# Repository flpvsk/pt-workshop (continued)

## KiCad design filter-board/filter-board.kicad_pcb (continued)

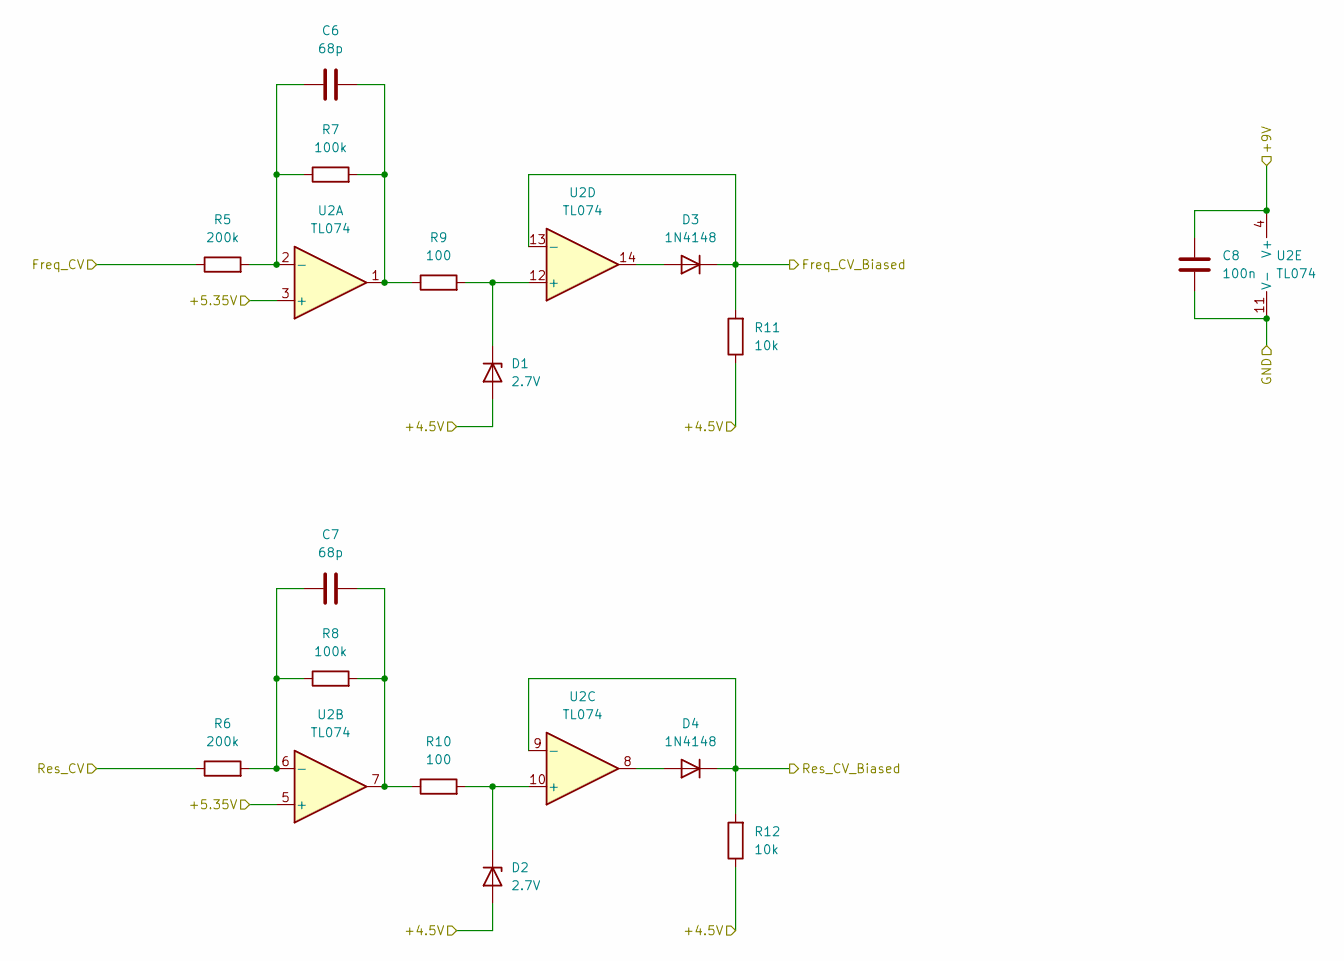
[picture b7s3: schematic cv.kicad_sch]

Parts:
C6, C7: 68p; C_0603_1608Metric_Pad1.08x0.95mm_HandSolder; LCSC C1680
C8: 100n; C_0603_1608Metric_Pad1.08x0.95mm_HandSolder; LCSC C76711
D1, D2: 2.7V; D_SOD-123; LCSC C406712
D3, D4: 1N4148; D_SOD-123; LCSC C81598
R5, R6: 200k; R_0603_1608Metric_Pad0.98x0.95mm_HandSolder; LCSC C25811
R7, R8: 100k; R_0603_1608Metric_Pad0.98x0.95mm_HandSolder; LCSC C25803
R9, R10: 100; R_0603_1608Metric_Pad0.98x0.95mm_HandSolder; LCSC C22775
R11, R12: 10k; R_0603_1608Metric_Pad0.98x0.95mm_HandSolder; LCSC C25804
U2: TL074; SOIC-14_3.9x8.7mm_P1.27mm; LCSC C6963

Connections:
/+4.5V_Buf: D1.2 (A), D2.2 (A), R11.1, R12.1; also elsewhere on the board
/+5.35V_Buf: U2.3 (+), U2.5 (+); also elsewhere on the board
/+9V: C8.2, U2.4 (V+); also elsewhere on the board
/CV Processing/Freq_CV_Biased: D3.1 (K), R11.2, U2.13 (-); also elsewhere on the board
/CV Processing/Res_CV_Biased: D4.1 (K), R12.2, U2.9 (-); also elsewhere on the board
/Freq_CV: R5.1; also elsewhere on the board
/GND: C8.1, U2.11 (V-); also elsewhere on the board
/Res_CV: R6.1; also elsewhere on the board
unnamed: C6.1, R5.2, R7.1, U2.2 (-)
unnamed: C6.2, R7.2, R9.1, U2.1
unnamed: C7.1, R6.2, R8.1, U2.6 (-)
unnamed: C7.2, R8.2, R10.1, U2.7
unnamed: D1.1 (K), R9.2, U2.12 (+)
unnamed: D2.1 (K), R10.2, U2.10 (+)
unnamed: D3.2 (A), U2.14
unnamed: D4.2 (A), U2.8

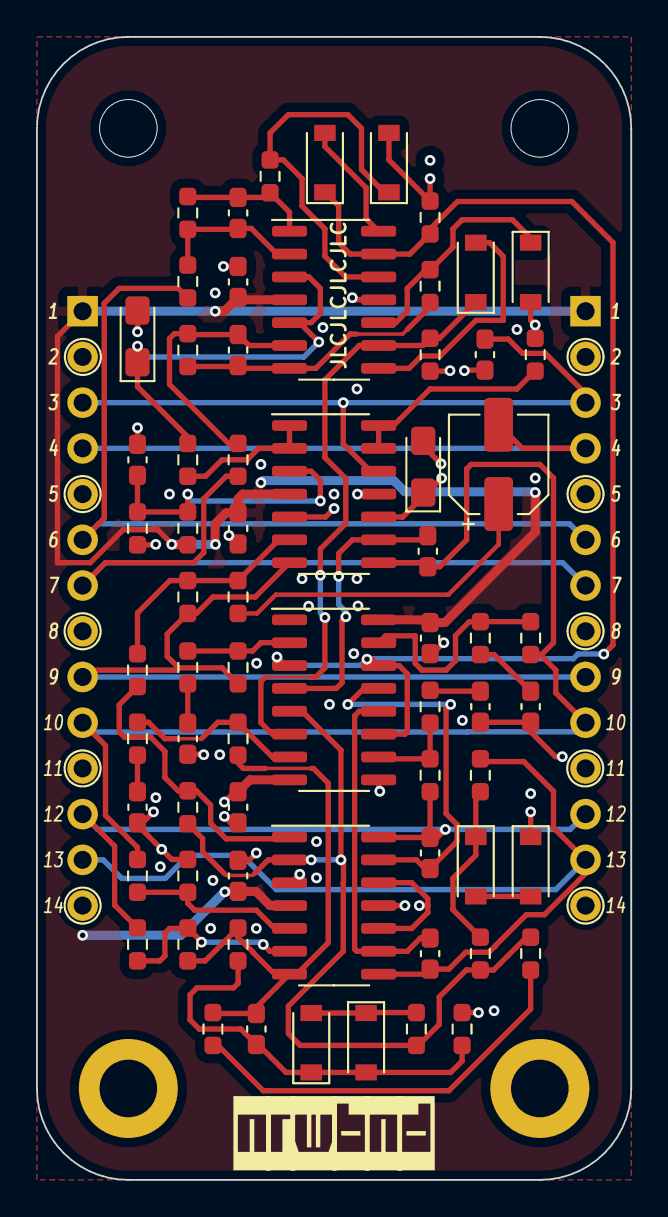
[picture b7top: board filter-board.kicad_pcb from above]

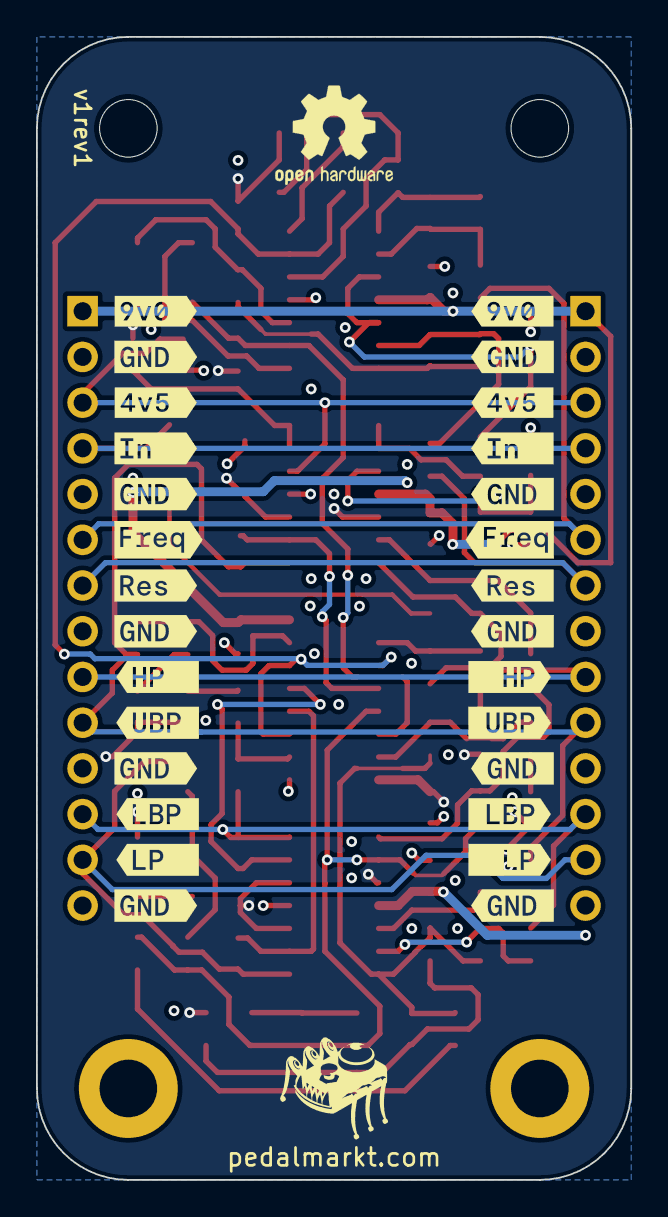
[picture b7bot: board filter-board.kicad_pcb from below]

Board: 4 copper layers, 33.0 x 63.5 mm, 102 parts (30 on the bottom side), 48 nets.

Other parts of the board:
kibuzzard-666B0D3F: G***; kibuzzard-666B0D3F
kibuzzard-666B0D4B, kibuzzard-666B0D4B#2, kibuzzard-666B0D4B#3, kibuzzard-666B0D4B#4, kibuzzard-666B0D4B#5: G***; kibuzzard-666B0D4B
kibuzzard-666B0D6E: G***; kibuzzard-666B0D6E
kibuzzard-666B0D54: G***; kibuzzard-666B0D54
kibuzzard-666B0D65: G***; kibuzzard-666B0D65
kibuzzard-666B0D69, kibuzzard-666B0D69#2, kibuzzard-666B0D69#3, kibuzzard-666B0D69#4, kibuzzard-666B0D69#5: G***; kibuzzard-666B0D69
kibuzzard-666D7707: G***; kibuzzard-666D7707
kibuzzard-6673DFE6: G***; kibuzzard-6673DFE6
kibuzzard-6673E32C: G***; kibuzzard-6673E32C
kibuzzard-6673E33D: G***; kibuzzard-6673E33D
kibuzzard-6673E38A: G***; kibuzzard-6673E38A
kibuzzard-6673E097: G***; kibuzzard-6673E097
kibuzzard-6673E301: G***; kibuzzard-6673E301
kibuzzard-6673E306: G***; kibuzzard-6673E306
kibuzzard-6673E326: G***; kibuzzard-6673E326
kibuzzard-6673E332: G***; kibuzzard-6673E332
kibuzzard-6673E338: G***; kibuzzard-6673E338
kibuzzard-6673E342: G***; kibuzzard-6673E342
kibuzzard-6673E377: G***; kibuzzard-6673E377
kibuzzard-6673E380: G***; kibuzzard-6673E380
kibuzzard-6673E386: G***; kibuzzard-6673E386

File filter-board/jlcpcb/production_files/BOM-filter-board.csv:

Comment,Designator,Footprint,LCSC
220p,"C10,C13,C15,C18",C_0603_1608Metric_Pad1.08x0.95mm_HandSolder,C106210
22u,"C3,C4",CP_EIA-3216-18_Kemet-A_Pad1.58x1.35mm_HandSolder,C129272
68p,"C6,C7",C_0603_1608Metric_Pad1.08x0.95mm_HandSolder,C1680
100,"R10,R9",R_0603_1608Metric_Pad0.98x0.95mm_HandSolder,C22775
10,"R3,R4",R_0603_1608Metric_Pad0.98x0.95mm_HandSolder,C22859
220,"R24,R25,R27,R34",R_0603_1608Metric_Pad0.98x0.95mm_HandSolder,C22962
3.3k,"R28,R35",R_0603_1608Metric_Pad0.98x0.95mm_HandSolder,C22978
30k,R32,R_0603_1608Metric_Pad0.98x0.95mm_HandSolder,C22984
330k,R31,R_0603_1608Metric_Pad0.98x0.95mm_HandSolder,C23137
6.8k,R1,R_0603_1608Metric_Pad0.98x0.95mm_HandSolder,C23212
100k,"R7,R8",R_0603_1608Metric_Pad0.98x0.95mm_HandSolder,C25803
10k,"R11,R12,R2",R_0603_1608Metric_Pad0.98x0.95mm_HandSolder,C25804
200k,"R5,R6",R_0603_1608Metric_Pad0.98x0.95mm_HandSolder,C25811
22k,R23,R_0603_1608Metric_Pad0.98x0.95mm_HandSolder,C31850
2.7V,"D1,D2,D7,D8",D_SOD-123,C406712
33k,"R13,R14,R15,R16,R17,R18,R19,R20,R21,R22,R26,R29,R30,R33",R_0603_1608Metric_Pad0.98x0.95mm_HandSolder,C4216
1.2n,"C11,C12,C14,C16",C_0603_1608Metric_Pad1.08x0.95mm_HandSolder,C576816
TL074,"U1,U2,U3",SOIC-14_3.9x8.7mm_P1.27mm,C6963
10u,C9,CP_Elec_5x5.4,C72486
100n,"C1,C17,C19,C2,C20,C5,C8",C_0603_1608Metric_Pad1.08x0.95mm_HandSolder,C76711
1N4148,"D3,D4,D5,D6",D_SOD-123,C81598
1,H2,MountingHole_3.2mm_M3,
GND,H3,MountingHole_3.2mm_M3_ISO14580_Pad,
2,H4,MountingHole_3.2mm_M3,
SSI2164-Split,U4,SOIC-16_3.9x9.9mm_P1.27mm,
GND,H1,MountingHole_3.2mm_M3_ISO14580_Pad,
Conn_01x14_Male,J1,PinHeader_1x14_P2.54mm_Vertical,
Conn_01x14_Male,J2,PinHeader_1x14_P2.54mm_Vertical,

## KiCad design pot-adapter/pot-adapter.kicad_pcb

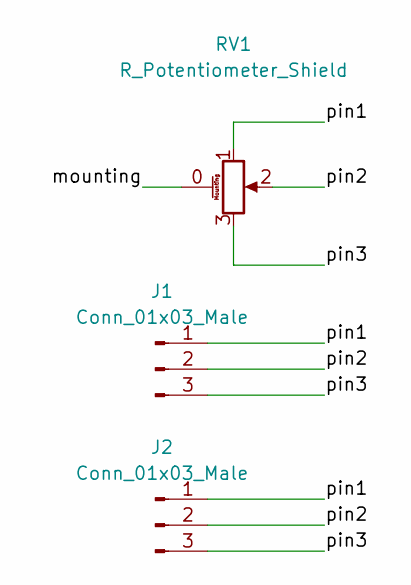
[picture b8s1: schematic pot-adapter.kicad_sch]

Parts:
J1, J2: Conn_01x03_Male; PinHeader_1x03_P2.54mm_Vertical
RV1: R_Potentiometer_Shield; V3_TRIM_R0904NB10KL-Keepout

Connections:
/mounting: RV1.0 (ShieldPin)
/pin1: J1.1, J2.1, RV1.1
/pin2: J1.2, J2.2, RV1.2
/pin3: J1.3, J2.3, RV1.3

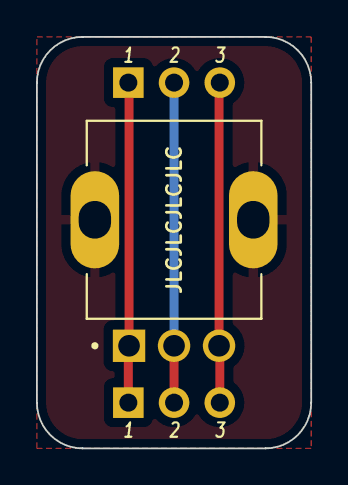
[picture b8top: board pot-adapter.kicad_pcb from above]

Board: 2 copper layers, 15.2 x 22.9 mm, 3 parts (0 on the bottom side), 3 nets.

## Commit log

2024-01-17 schem for the pt board
2024-01-18 10 pin socket
2024-01-18 Board layed out
2024-01-20 Mapped components
2024-01-20 v1rev1?
2024-02-02 lfo schem
2024-02-22 IO Board wip
2024-02-22 Mounting holes
2024-02-22 Design
2024-02-22 graphics
2024-02-24 Fixed buffers
2024-03-20 Before removing attenuverters
2024-03-20 PTT without attverts
2024-03-21 LFO graphics
2024-03-21 wip attenuverters
2024-03-22 Attvert board layout
2024-03-22 Attvert graphics
2024-03-22 AttVert pre-jlc
2024-03-22 AttVert JLCPCB order
2024-03-22 LFO board jlc
2024-03-23 Add gnd circles
2024-03-23 Add gnd circles attvert
2024-03-23 Attvert version on the board
2024-03-23 io jlc part numbers
2024-03-23 Add jlc num to io board
2024-05-22 JLC got 100n caps
2024-06-11 PTT schem export
2024-06-11 PTT instructions
2024-06-11 Schematic link
2024-06-12 VCA components linked
2024-06-13 VCA board components placed
2024-06-13 VCA board routing done
2024-06-13 Filter board schem done
2024-06-14 Filter board layout
2024-06-15 Filter board layout done
2024-06-17 Follower schem done
2024-06-19 Follower layout done
2024-06-20 Pot Adapter v1rev1
2024-06-20 VCA board ordered
2024-06-20 Filter board ordered
2024-06-20 Follower board ordered
2024-10-05 Protato updates and schem
2024-11-07 Remove D from linear VCA + update graphics
2024-11-07 JLC order placed
2024-12-06 Osc init
2024-12-27 wip pre-redo orientation
2024-12-27 OSC board layout done
2024-12-27 Hide refs
2025-01-03 Carrier ordered
2025-01-13 Carrier: notes after testing
2025-09-22 Add TODOs
2025-09-24 Longwave docs
2025-09-24 PTT example schem
